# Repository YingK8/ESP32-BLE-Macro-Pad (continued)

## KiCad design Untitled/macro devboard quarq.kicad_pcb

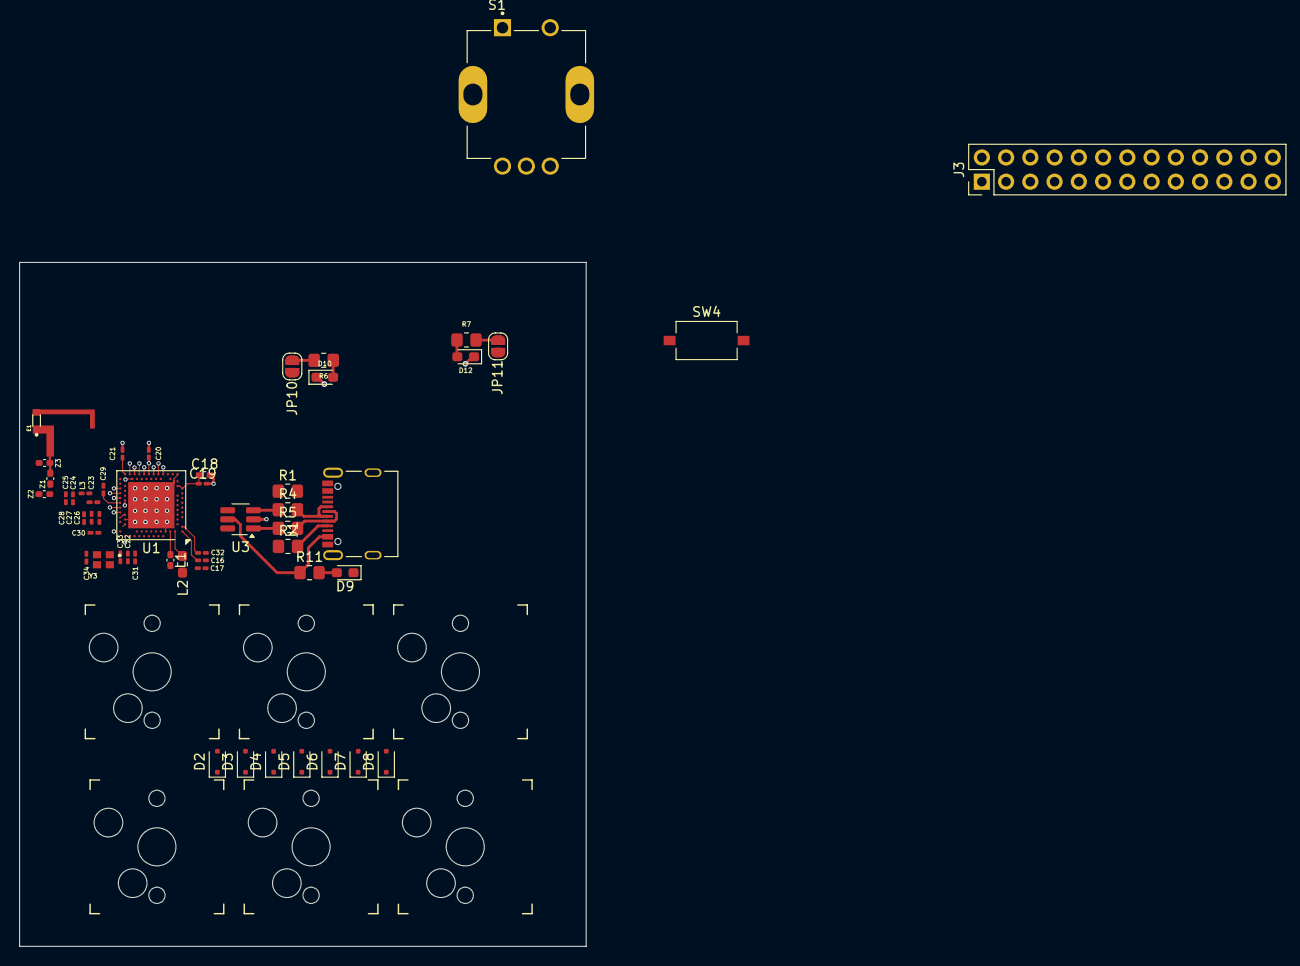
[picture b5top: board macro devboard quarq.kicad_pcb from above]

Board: 2 copper layers, 59.4 x 71.6 mm, 58 parts (0 on the bottom side), 42 nets.

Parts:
C16, C27: 1uF; C_0201_0603Metric_Pad0.64x0.40mm_HandSolder
C17, C19, C20, C21, C22, C30, C32: 100nF; C_0201_0603Metric_Pad0.64x0.40mm_HandSolder
C18: 4.7uF; C_0402_1005Metric_Pad0.74x0.62mm_HandSolder
C23: 0.8pF; C_0201_0603Metric_Pad0.64x0.40mm_HandSolder
C24: 0.5pF; C_0201_0603Metric_Pad0.64x0.40mm_HandSolder
C25, C26, C31: DNF; C_0201_0603Metric_Pad0.64x0.40mm_HandSolder
C28: 47nF; C_0201_0603Metric_Pad0.64x0.40mm_HandSolder
C29: 820pF; C_0201_0603Metric_Pad0.64x0.40mm_HandSolder
C33, C34: 8pF; C_0201_0603Metric_Pad0.64x0.40mm_HandSolder
D2, D3, D4, D5, D6, D7, D8: 1N4148WT; D_SOD-323F
D9, D10, D12: LED; LED_0603_1608Metric_Pad1.05x0.95mm_HandSolder
E1: 2450AT14A0100001T; XDCR_AMCA31-2R450G-S1F-T3
J1: 12402012E212A; AMPHENOL_12402012E212A
J3: Conn_02x13_Counter_Clockwise; PinHeader_2x13_P2.54mm_Vertical
JP10, JP11: SolderJumper_2_Open; SolderJumper-2_P1.3mm_Open_RoundedPad1.0x1.5mm
L1: 15nH; L_0402_1005Metric_Pad0.77x0.64mm_HandSolder
L2: 10uH; L_0603_1608Metric_Pad1.05x0.95mm_HandSolder
L3: 4.7nH; L_0201_0603Metric_Pad0.64x0.40mm_HandSolder
R1, R2: 5.1k; R_0805_2012Metric_Pad1.20x1.40mm_HandSolder
R4, R5: 22; R_0805_2012Metric_Pad1.20x1.40mm_HandSolder
R6, R7, R11: 100; R_0805_2012Metric_Pad1.20x1.40mm_HandSolder
S1: PEC12R-4225F-S0024; XDCR_PEC12R-4225F-S0024
SW1, SW2, SW6, SW7, SW8, SW9: MX_SW_HS; Kailh_socket_MX
SW4: RST; SW_Tactile_SPST_NO_Straight_CK_PTS636Sx25SMTRLFS
U1: nRF52840; Nordic_AQFN-73-1EP_7x7mm_P0.5mm
U3: USBLC6-2SC6; SOT-23-6_Handsoldering
Y3: ECS-320-8-37B-CKY-TR; XTAL_ECS-160-9-37-CKM-TR
Z1: 7.5nH; L_0402_1005Metric_Pad0.77x0.64mm_HandSolder
Z2: DNF; C_0402_1005Metric_Pad0.74x0.62mm_HandSolder
Z3: 0.6pF; C_0402_1005Metric_Pad0.74x0.62mm_HandSolder

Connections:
+5V: C16.1, C17.1, C18.1, C19.1, C20.1, C21.1, C22.1, J1.A4_B9 (VBUS), J3.1, J3.25, J3.26, R11.1, U1.A22 (VDD), U1.AD14 (VDD), U1.AD23 (VDD), U1.B1 (VDD), U1.W1 (VDD), U1.Y2 (VDDH), U3.5 (VBUS)
/Din+: J1.A6 (D+_A), J1.B6 (D+_B), R4.2
/Din-: J1.A7 (D-_A), J1.B7 (D-_B), R5.2
ANT: C24.1, C25.1, L3.1, Z1.1, Z2.1
D+: U1.AD6 (D+), U3.4 (I/O2)
D-: U1.AD4 (D-), U3.6 (I/O1)
DCDCIND1: L2.1, U1.B3 (DCC)
DCDCIND2: C26.1, C27.1, C28.1, L1.1, U1.B5 (DEC4), U1.E24 (DEC6)
GND: C16.2, C17.2, C18.2, C19.2, C20.2, C21.2, C22.2, C23.2, C24.2, C25.2, C26.2, C27.2, C28.2, C29.1, C30.1, C31.1, C32.1, C33.2, C34.2, D9.1 (K), D10.1 (K), D12.1 (K), J1.A1_B12 (GND), J1.A8 (SBU1), J1.B1_A12 (GND__1), J1.B8 (SBU2), J1.SH1 (SHIELD), J1.SH2 (SHIELD__1), J1.SH3 (SHIELD__2), J1.SH4 (SHIELD__3), J3.7, J3.13, J3.16, J3.19, R1.1, R2.1, S1.C (COMMON), S1.SH1 (SHIELD), S1.SH2 (SHIELD__1), SW4.2, U1.AD2 (VBUS), U1.B7 (VSS), U1.EP (VSS), U1.F23 (VSS_PA), U3.2 (GND), Y3.2 (GND), Y3.4 (GND__1), Z2.2, Z3.2
unnamed: D2.2 (A), SW1.2
unnamed: D3.2 (A), SW6.2
unnamed: D4.2 (A), SW7.2
unnamed: D5.2 (A), SW8.2
unnamed: D6.2 (A), SW9.2
unnamed: D7.2 (A), SW2.2
unnamed: D8.2 (A), S1.1
unnamed: D9.2 (A), R11.2
unnamed: D10.2 (A), R6.1
unnamed: D12.2 (A), R7.1
unnamed: E1.1, Z1.2, Z3.1
unnamed: J1.A5 (CC1_A), R2.2
unnamed: J1.B5 (CC1_B), R1.2
unnamed: JP10.1 (A), R6.2
unnamed: JP11.1 (A), R7.2
unnamed: L1.2, L2.2
unnamed: R4.1, U3.3 (I/O2)
unnamed: R5.1, U3.1 (I/O1)
unnamed: C23.1, L3.2, U1.H23 (ANT)
unnamed: C32.2, U1.C1 (DEC1)
unnamed: C31.2, U1.A18 (DEC2)
unnamed: C30.2, U1.D23 (DEC3)
unnamed: C29.2, U1.N24 (DEC5)
unnamed: C33.1, U1.B24 (XC1), Y3.1 (IN/OUT)
unnamed: C34.1, U1.A23 (XC2), Y3.3 (OUT/IN)
PD4/LED2: J3.18, JP10.2 (B)
PF7/LED1: J3.17, JP11.2 (B)
RESET: SW4.1, U1.AC13 (P0.18/~RESET)
col0: SW6.1, SW8.1
col1: SW7.1, SW9.1
col2: SW1.1, SW2.1
row0: D2.1 (K), D3.1 (K), D4.1 (K), D8.1 (K)
row1: D5.1 (K), D6.1 (K), D7.1 (K)

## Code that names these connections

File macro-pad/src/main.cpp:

#include <Arduino.h>

#include "BLE_HID.h"
#include "Config.h"
#include "HostLink.h"
#include "MacroPad.h"
#include "Rotary_Encoder.h"
#include "Screen.h"

BLE_HID  ble;
Screen   screen;
HostLink host;

// Rows driven LOW one at a time; cols read with INPUT_PULLUP. Index = r*COLS + c.
//                  col0=GPIO4    col1=GPIO21    col2=GPIO8
//   row0=GPIO1:    [PREV APP]    [SCREENSHOT]   [NEXT APP]
//   row1=GPIO5:    [ACTION A]    [SPOTLIGHT]    [ACTION B]
//
// Col 1 is GPIO21 = UART0 TX, which the peripheral may hold HIGH; the two keys
// there are the expendable ones for that reason. The four host keys sit on the
// columns known to scan reliably.
static Key keymap[ROWS * COLS] = {
    Key::app(AppKey::PREV),
    Key::combo(Mod::LGUI | Mod::LSHIFT, BLE_HID::charToHidCode('4')),  // macOS: capture selection
    Key::app(AppKey::NEXT),

    Key::app(AppKey::ACTION_A),
    Key::combo(Mod::LGUI, BLE_HID::charToHidCode(' ')),                // macOS: Spotlight
    Key::app(AppKey::ACTION_B)
};

MacroPad keypad(ble, keymap, ROWS, COLS, ROW_PINS, COL_PINS);
Encoder  encoder(ble, PIN_ENCODER_A, PIN_ENCODER_B);

// Set by each frame: when true the host wants encoder deltas instead of HID volume.
static bool encoderToHost = false;

// Last fallback message drawn, or nullptr while a host frame is on screen. Both
// messages are string literals, so comparing pointers is enough to detect a
// change — without this the fallback would repaint on every one of the ~200 loop
// iterations per second, and would never notice BLE connecting.
static const char* statusShown = nullptr;

// Runs before MacroPad's own HID dispatch. Returning true consumes the key, so
// AppKey entries never reach the BLE path — they are ours alone.
static bool onKeyEvent(const Key& key, bool pressed) {
    if (key.type != KeyType::APP) return false;
    screen.noteActivity();
    host.sendKey(key._app, pressed);
    return true;
}

void setup() {
    Serial.begin(115200);
    host.begin();
    screen.begin();
    screen.showStatus("MACROPAD", "waiting for host...");

    ble.begin("ESP32 MacroPad");
    ble.startAdvertising();  // last: NimBLE freezes the GATT table once the server starts
    keypad.begin();
    keypad.setKeyHandler(onKeyEvent);
    encoder.begin();
}

void loop() {
    ble.tick();  // flush any deferred media-key release from the previous iteration

    JsonDocument frame;
    if (host.poll(frame)) {
        encoderToHost = frame["e"].as<int>() != 0;
        screen.drawFrame(frame["l"].as<JsonArrayConst>());
        statusShown = nullptr;
    } else if (!host.hostPresent()) {
        const char* detail = ble.isConnected() ? "BLE ok - no host app"
                                               : "waiting for host...";
        if (detail != statusShown) {
            screen.showStatus("MACROPAD", detail);
            statusShown = detail;
        }
    }

    keypad.handleKeypad();

    encoder.handle();
    int delta = encoder.consumeDelta();
    if (delta != 0) {
        screen.noteActivity();
        if (encoderToHost) {
            // Flip the sign here if scrolling on the pad feels backwards.
            host.sendEncoder(delta);
        } else {
            while (delta < 0) { ble.sendMediaKey(MediaKey::VOL_UP);   delta++; }
            while (delta > 0) { ble.sendMediaKey(MediaKey::VOL_DOWN); delta--; }
        }
    }

    screen.tick();
    delay(5);
}

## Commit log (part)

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2025-07-02 a bunch of work
2025-07-02 more changesmore changes
2025-07-06 humidifier
2025-08-26 used keypad, which doesn't work
2025-08-26 key register working!
2025-09-08 Revert "key register working!"
    This reverts commit 267d64cb3103f37808471bd2d2e793a2cff04a2e.
2025-09-13 keystrokes + encoder working
2025-09-13 everything working
2025-09-14 encoder good
2025-09-14 dleted some files
2025-09-14 set up example
2025-09-15 fixed GPIOs for SPI
2025-09-15 reorganised
2025-09-15 morechanges
2025-09-20 seperated code into modules
2025-09-20 cleaned up directory
2025-09-20 cleaned up post merge
2025-09-21 modules working
2026-05-17 refactored code
2026-05-19 copilot: LVGL UI
2026-05-20 this was the actual printed PCB design
2026-05-20 updated pin assignment
2026-05-23 claude code redesign
2026-05-24 cleaned up
2026-05-24 working design
2026-05-30 removed old file
2026-06-04 buttons work again mostly
2026-06-05 working UI
2026-06-06 smaller ble + task sending
